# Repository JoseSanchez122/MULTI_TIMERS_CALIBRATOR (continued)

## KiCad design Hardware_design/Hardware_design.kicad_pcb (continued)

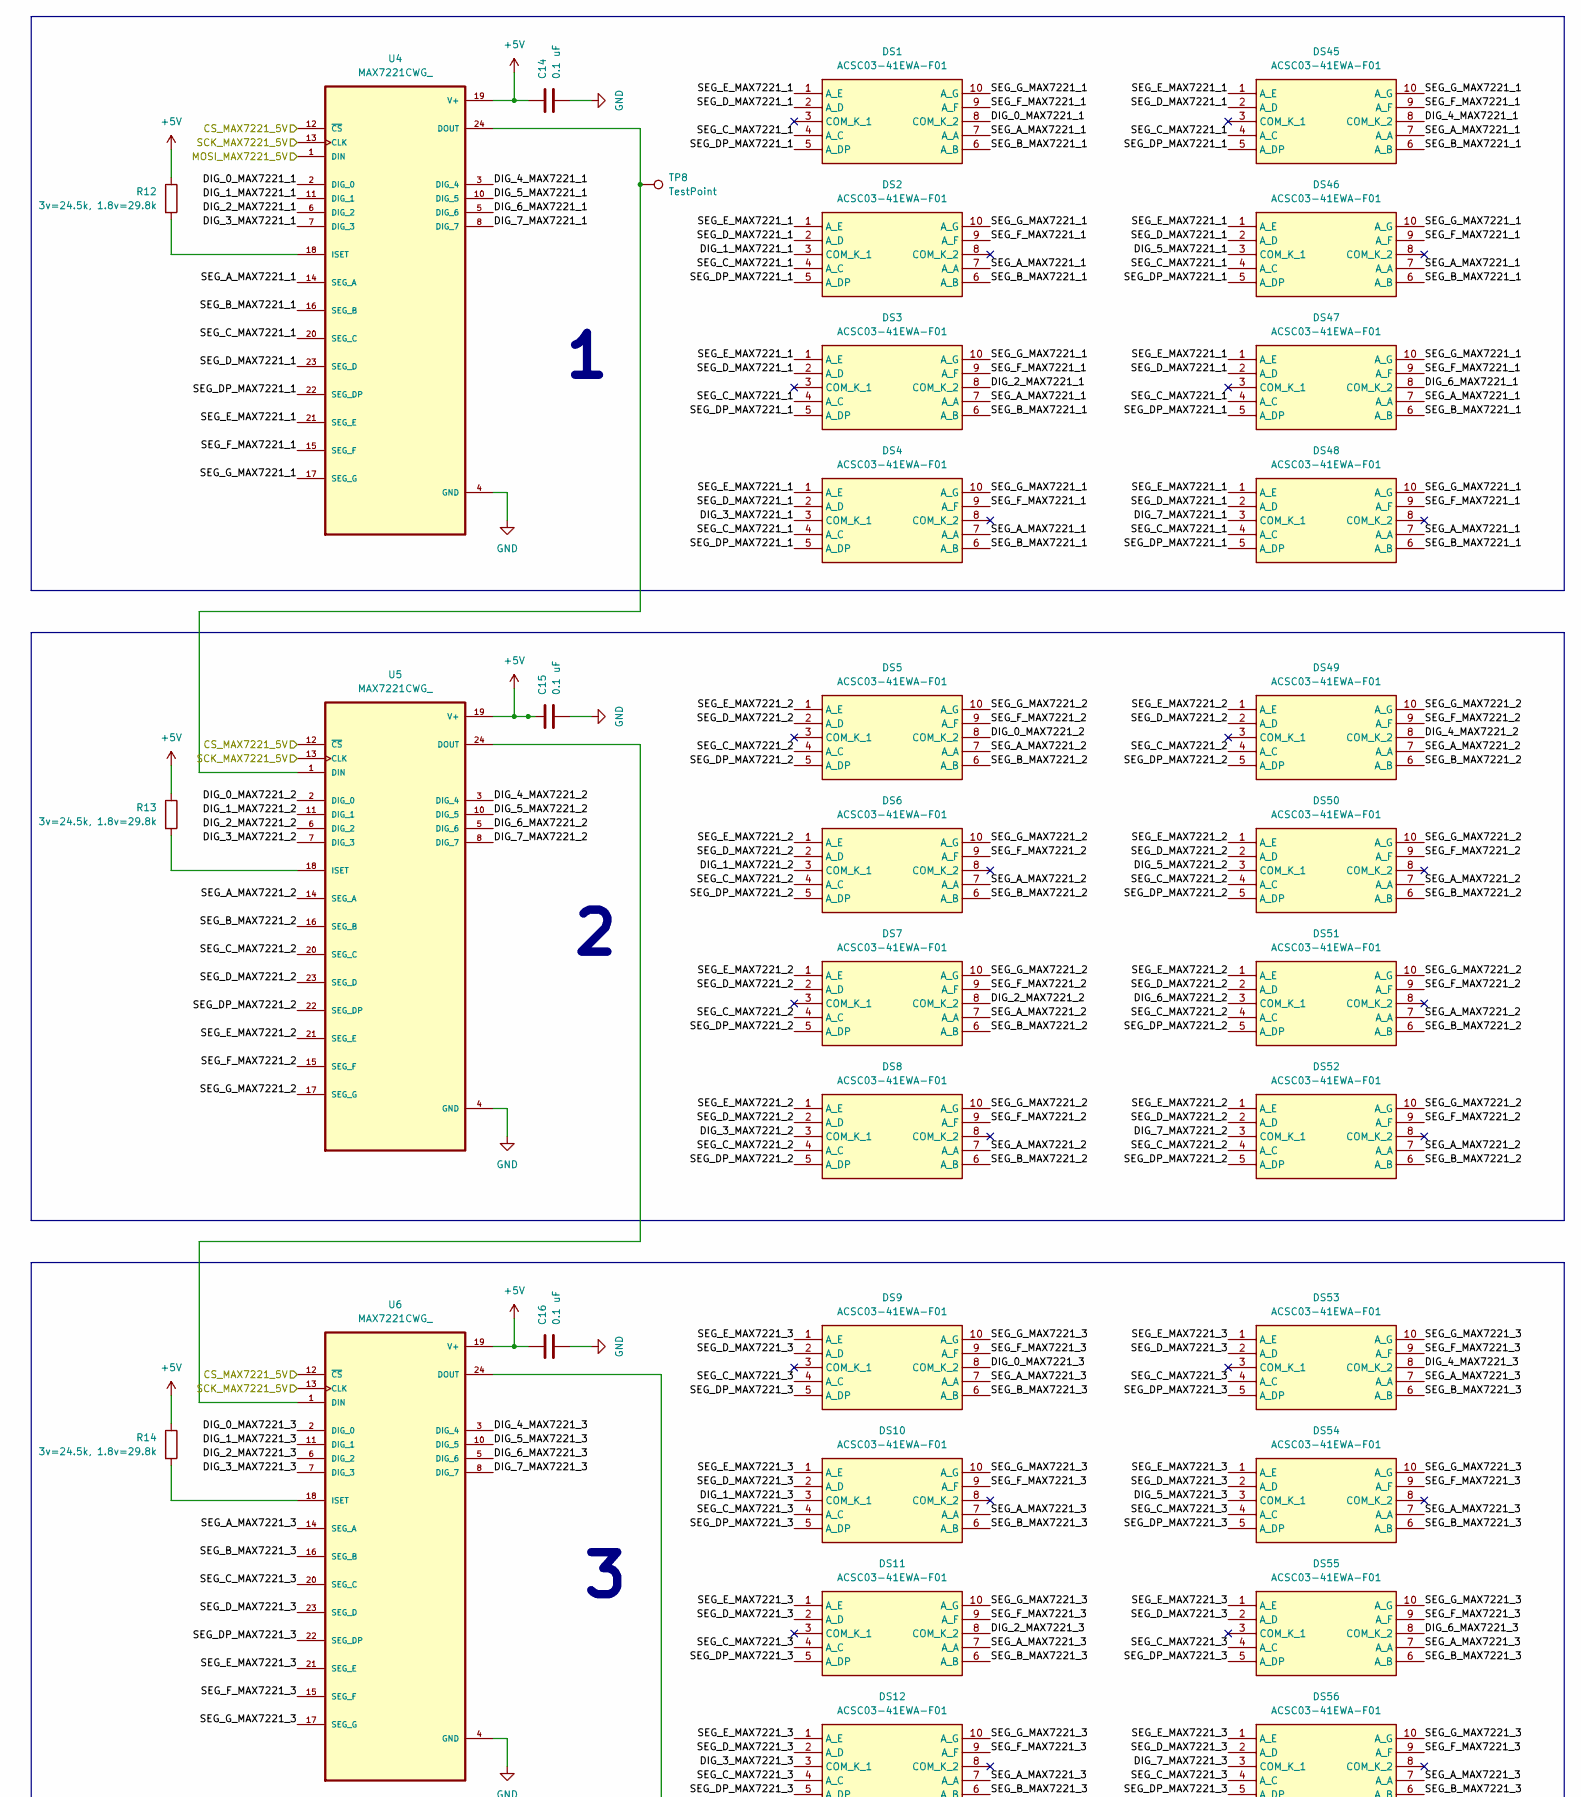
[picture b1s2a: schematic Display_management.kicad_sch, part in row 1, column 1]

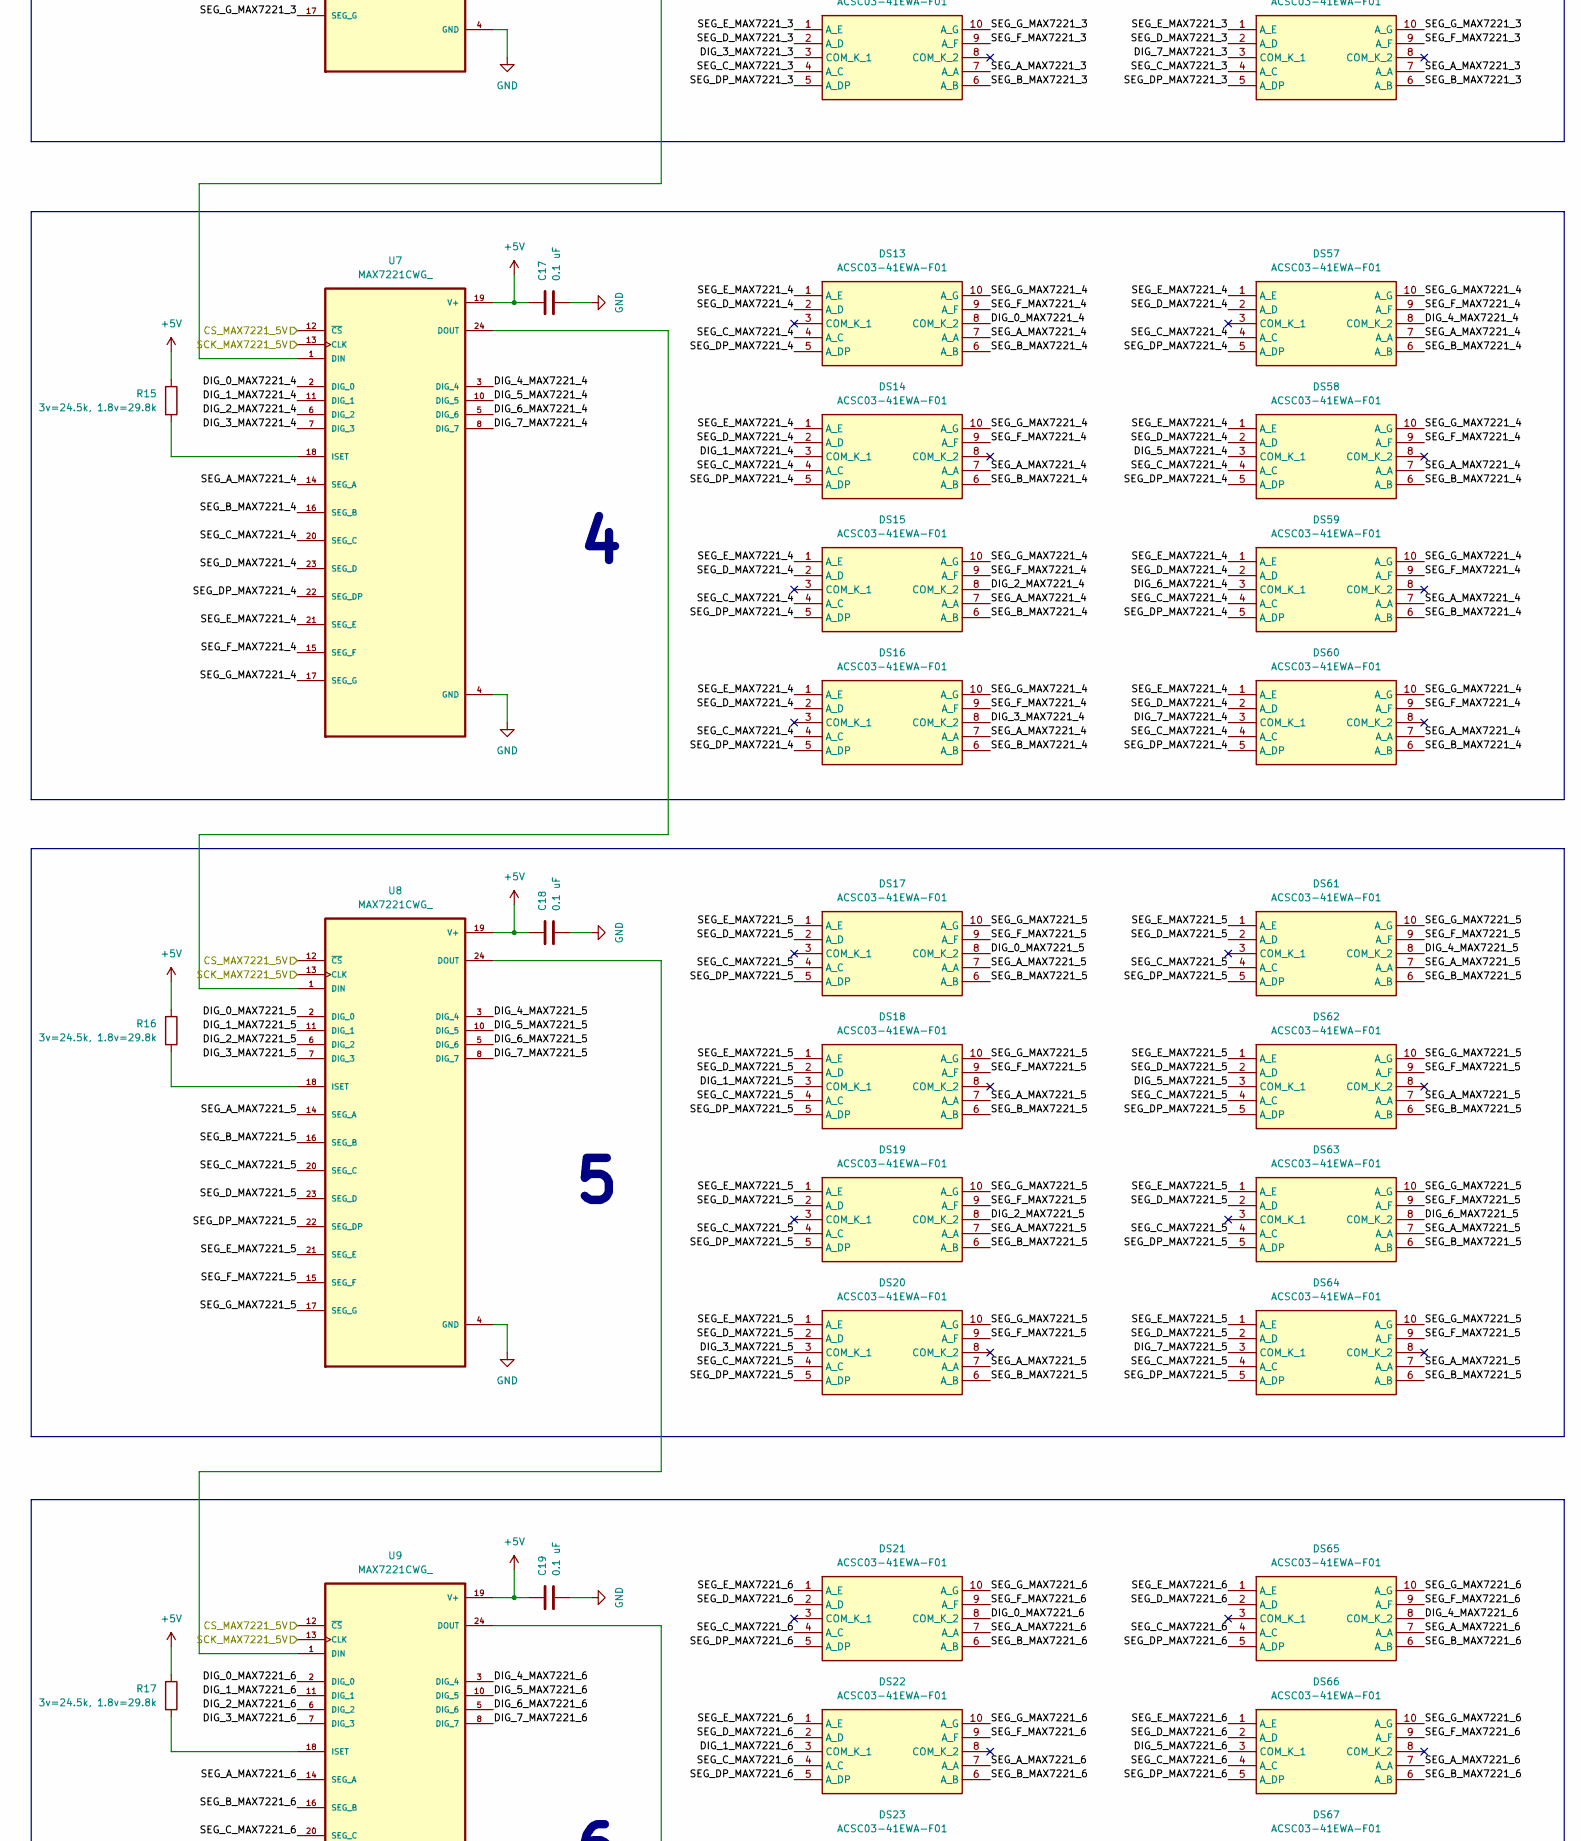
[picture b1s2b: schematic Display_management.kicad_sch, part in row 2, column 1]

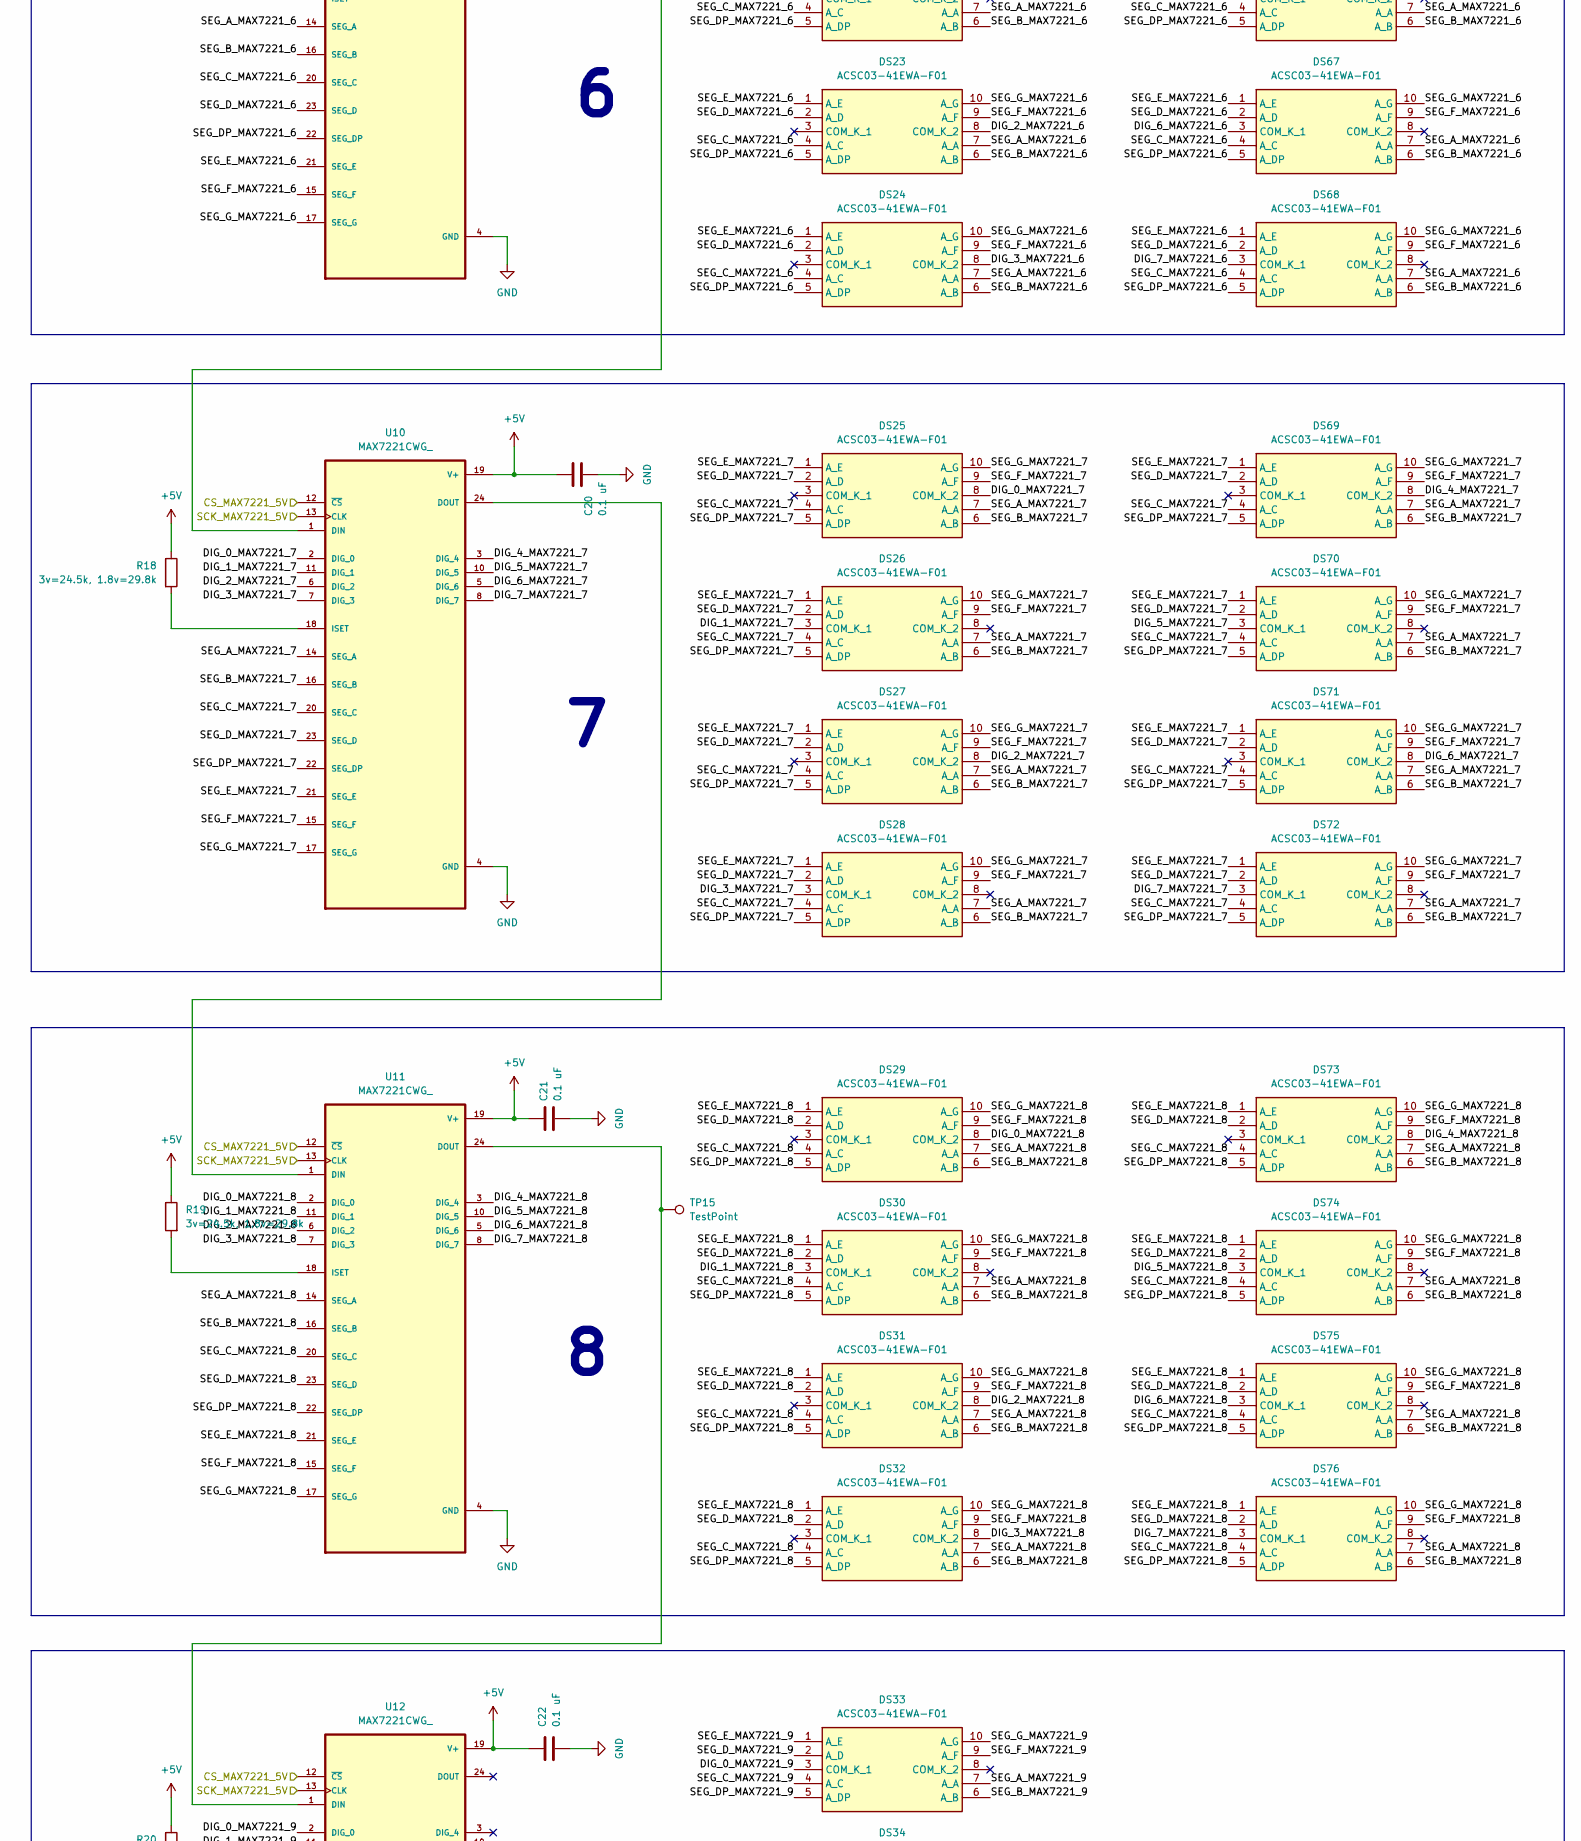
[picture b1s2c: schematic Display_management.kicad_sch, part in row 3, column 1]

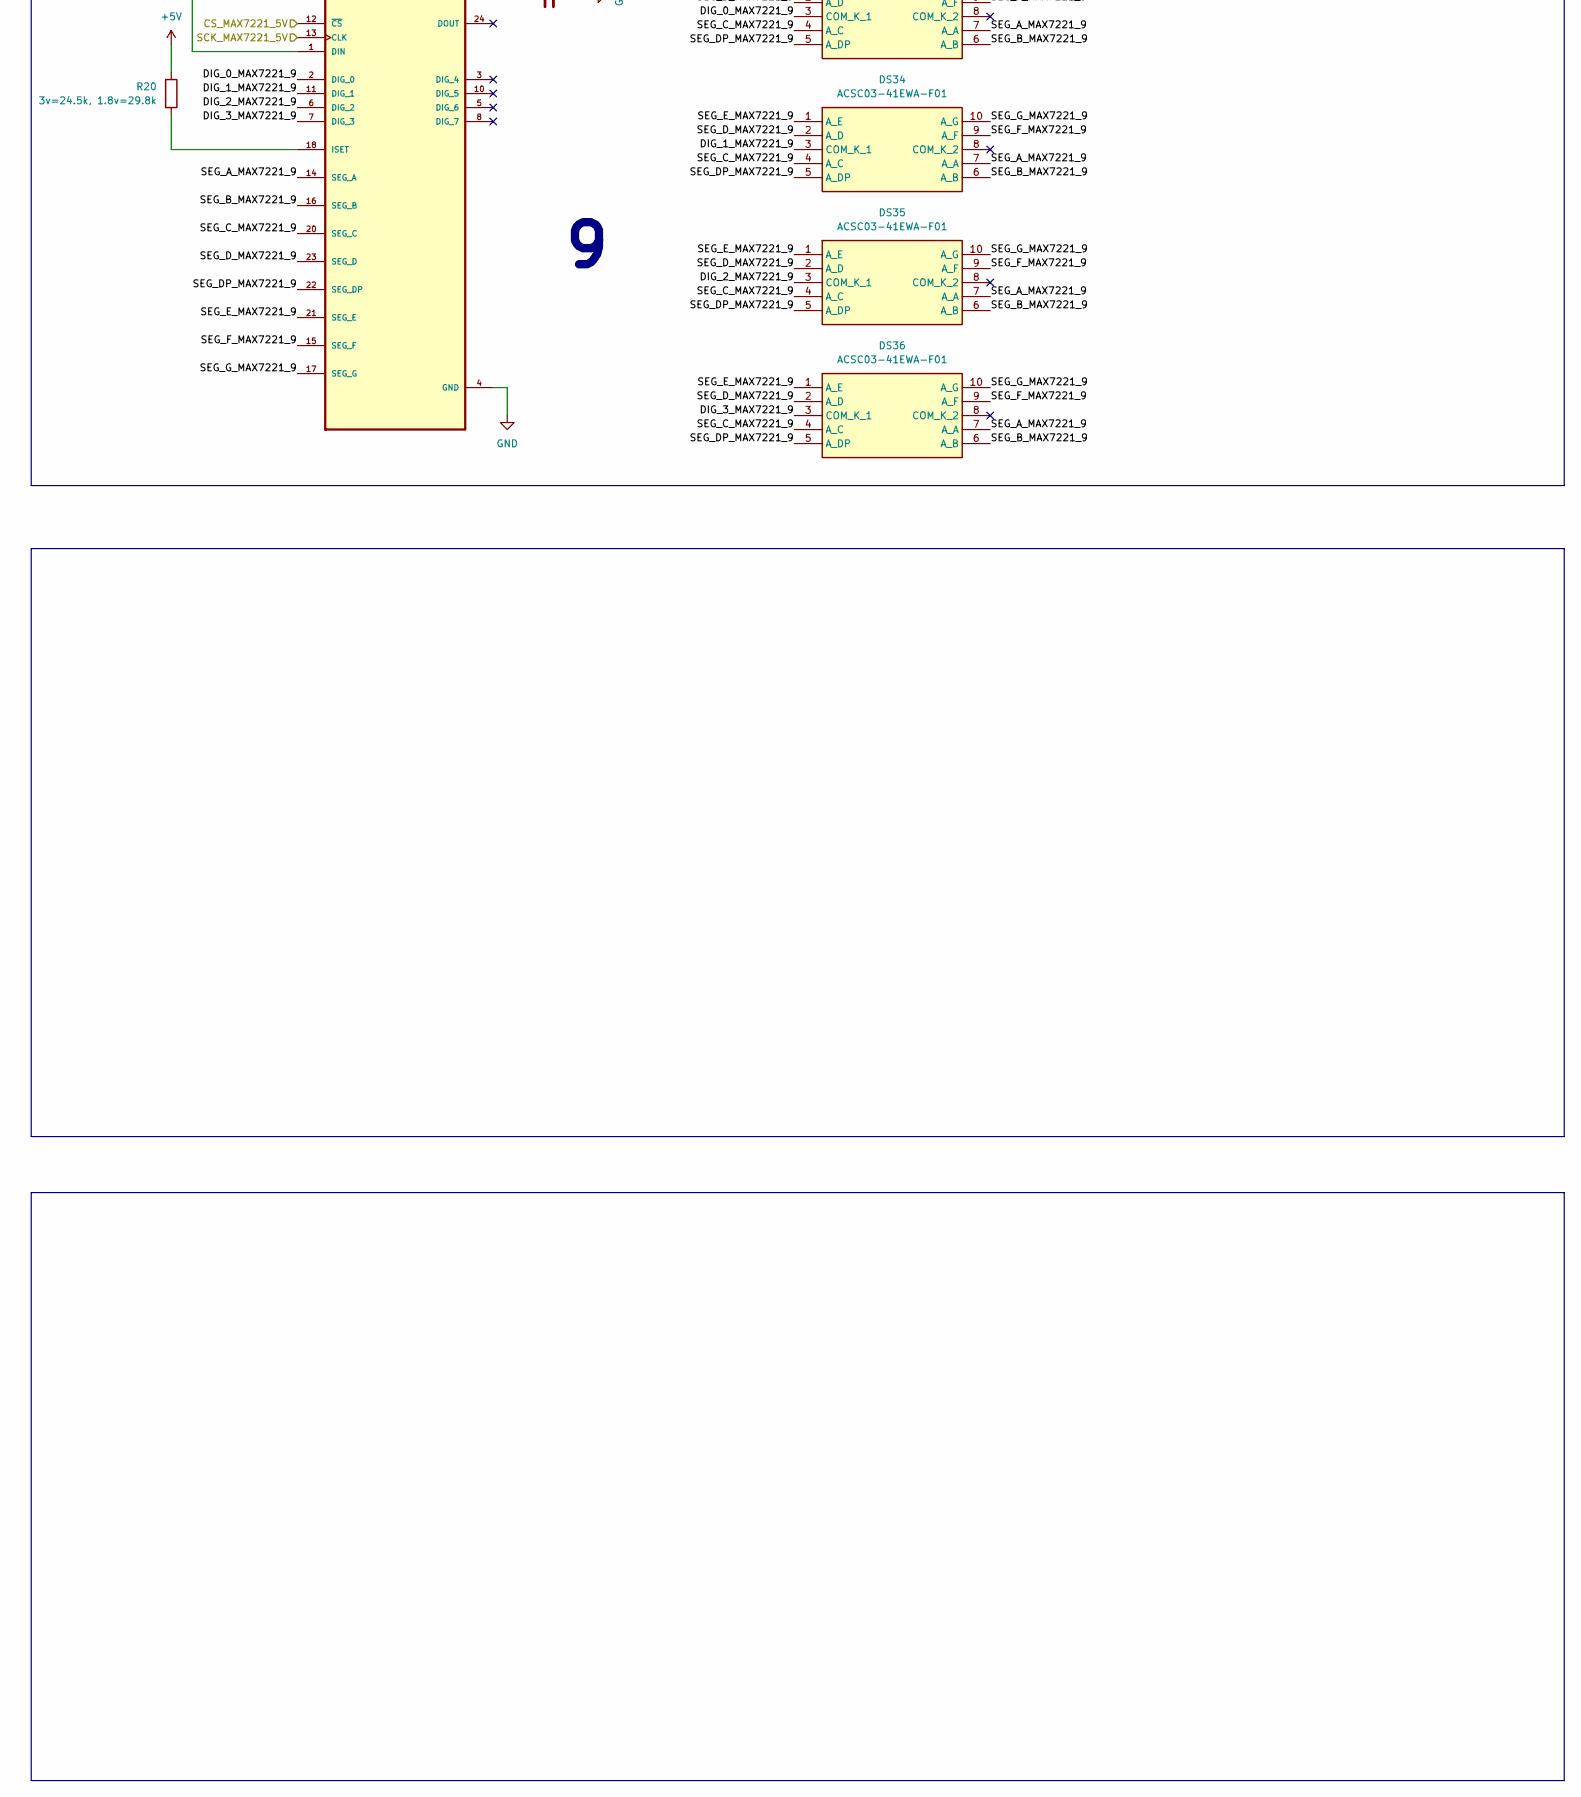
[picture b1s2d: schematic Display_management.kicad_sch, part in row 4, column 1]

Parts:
C14, C15, C16, C17, C18, C19, C20, C21, C22: 0.1 uF; 0805_SMD_CERAMIC_CAP_T491B106K016AT
DS1, DS2, DS3, DS4, DS5, DS6, DS7, DS8, DS9, DS10, DS11, DS12, DS13, DS14, DS15, DS16, DS17, DS18, DS19, DS20, DS21, DS22, DS23, DS24, DS25, DS26, DS27, DS28, DS29, DS30, DS31, DS32, DS33, DS34, DS35, DS36, DS45, DS46, DS47, DS48, DS49, DS50, DS51, DS52, DS53, DS54, DS55, DS56, DS57, DS58, DS59, DS60, DS61, DS62, DS63, DS64, DS65, DS66, DS67, DS68, DS69, DS70, DS71, DS72, DS73, DS74, DS75, DS76: ACSC03-41EWA-F01; SMD_DISPLAY_ACSC03-41EWA-F01; Mouser Part Number 604-ACSC03-41EWA-F01
R12, R13, R14, R15, R16, R17, R18, R19, R20: 3v=24.5k, 1.8v=29.8k; 0805_RES_RESC2012X60N
TP8, TP15: TestPoint; TestPoint_Pad_1.0x1.0mm
U4, U5, U6, U7, U8, U9, U10, U11, U12: MAX7221CWG_; Disp_Controler_MAX7221CWG_

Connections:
+5V: C14.1, C15.1, C16.1, C17.1, C18.1, C19.1, C20.1, C21.1, C22.1, R12.1, R13.1, R14.1, R15.1, R16.1, R17.1, R18.1, R19.1, R20.1, U4.19 (V+), U5.19 (V+), U6.19 (V+), U7.19 (V+), U8.19 (V+), U9.19 (V+), U10.19 (V+), U11.19 (V+), U12.19 (V+); also elsewhere on the board
/CS_MAX7221_5V: U4.12 (~CS), U5.12 (~CS), U6.12 (~CS), U7.12 (~CS), U8.12 (~CS), U9.12 (~CS), U10.12 (~CS), U11.12 (~CS), U12.12 (~CS); also elsewhere on the board
/Display_management/DIG_0_MAX7221_1: DS1.8 (COM_K_2), U4.2 (DIG_0)
/Display_management/DIG_0_MAX7221_2: DS5.8 (COM_K_2), U5.2 (DIG_0)
/Display_management/DIG_0_MAX7221_3: DS9.8 (COM_K_2), U6.2 (DIG_0)
/Display_management/DIG_0_MAX7221_4: DS13.8 (COM_K_2), U7.2 (DIG_0)
/Display_management/DIG_0_MAX7221_5: DS17.8 (COM_K_2), U8.2 (DIG_0)
/Display_management/DIG_0_MAX7221_6: DS21.8 (COM_K_2), U9.2 (DIG_0)
/Display_management/DIG_0_MAX7221_7: DS25.8 (COM_K_2), U10.2 (DIG_0)
/Display_management/DIG_0_MAX7221_8: DS29.8 (COM_K_2), U11.2 (DIG_0)
/Display_management/DIG_0_MAX7221_9: DS33.3 (COM_K_1), U12.2 (DIG_0)
/Display_management/DIG_1_MAX7221_1: DS2.3 (COM_K_1), U4.11 (DIG_1)
/Display_management/DIG_1_MAX7221_2: DS6.3 (COM_K_1), U5.11 (DIG_1)
/Display_management/DIG_1_MAX7221_3: DS10.3 (COM_K_1), U6.11 (DIG_1)
/Display_management/DIG_1_MAX7221_4: DS14.3 (COM_K_1), U7.11 (DIG_1)
/Display_management/DIG_1_MAX7221_5: DS18.3 (COM_K_1), U8.11 (DIG_1)
/Display_management/DIG_1_MAX7221_6: DS22.3 (COM_K_1), U9.11 (DIG_1)
/Display_management/DIG_1_MAX7221_7: DS26.3 (COM_K_1), U10.11 (DIG_1)
/Display_management/DIG_1_MAX7221_8: DS30.3 (COM_K_1), U11.11 (DIG_1)
/Display_management/DIG_1_MAX7221_9: DS34.3 (COM_K_1), U12.11 (DIG_1)
/Display_management/DIG_2_MAX7221_1: DS3.8 (COM_K_2), U4.6 (DIG_2)
/Display_management/DIG_2_MAX7221_2: DS7.8 (COM_K_2), U5.6 (DIG_2)
/Display_management/DIG_2_MAX7221_3: DS11.8 (COM_K_2), U6.6 (DIG_2)
/Display_management/DIG_2_MAX7221_4: DS15.8 (COM_K_2), U7.6 (DIG_2)
/Display_management/DIG_2_MAX7221_5: DS19.8 (COM_K_2), U8.6 (DIG_2)
/Display_management/DIG_2_MAX7221_6: DS23.8 (COM_K_2), U9.6 (DIG_2)
/Display_management/DIG_2_MAX7221_7: DS27.8 (COM_K_2), U10.6 (DIG_2)
/Display_management/DIG_2_MAX7221_8: DS31.8 (COM_K_2), U11.6 (DIG_2)
/Display_management/DIG_2_MAX7221_9: DS35.3 (COM_K_1), U12.6 (DIG_2)
/Display_management/DIG_3_MAX7221_1: DS4.3 (COM_K_1), U4.7 (DIG_3)
/Display_management/DIG_3_MAX7221_2: DS8.3 (COM_K_1), U5.7 (DIG_3)
/Display_management/DIG_3_MAX7221_3: DS12.3 (COM_K_1), U6.7 (DIG_3)
/Display_management/DIG_3_MAX7221_4: DS16.8 (COM_K_2), U7.7 (DIG_3)
/Display_management/DIG_3_MAX7221_5: DS20.3 (COM_K_1), U8.7 (DIG_3)
/Display_management/DIG_3_MAX7221_6: DS24.8 (COM_K_2), U9.7 (DIG_3)
/Display_management/DIG_3_MAX7221_7: DS28.3 (COM_K_1), U10.7 (DIG_3)
/Display_management/DIG_3_MAX7221_8: DS32.8 (COM_K_2), U11.7 (DIG_3)
/Display_management/DIG_3_MAX7221_9: DS36.3 (COM_K_1), U12.7 (DIG_3)
/Display_management/DIG_4_MAX7221_1: DS45.8 (COM_K_2), U4.3 (DIG_4)
/Display_management/DIG_4_MAX7221_2: DS49.8 (COM_K_2), U5.3 (DIG_4)
/Display_management/DIG_4_MAX7221_3: DS53.8 (COM_K_2), U6.3 (DIG_4)
/Display_management/DIG_4_MAX7221_4: DS57.8 (COM_K_2), U7.3 (DIG_4)
/Display_management/DIG_4_MAX7221_5: DS61.8 (COM_K_2), U8.3 (DIG_4)
/Display_management/DIG_4_MAX7221_6: DS65.8 (COM_K_2), U9.3 (DIG_4)
/Display_management/DIG_4_MAX7221_7: DS69.8 (COM_K_2), U10.3 (DIG_4)
/Display_management/DIG_4_MAX7221_8: DS73.8 (COM_K_2), U11.3 (DIG_4)
/Display_management/DIG_5_MAX7221_1: DS46.3 (COM_K_1), U4.10 (DIG_5)
/Display_management/DIG_5_MAX7221_2: DS50.3 (COM_K_1), U5.10 (DIG_5)
/Display_management/DIG_5_MAX7221_3: DS54.3 (COM_K_1), U6.10 (DIG_5)
/Display_management/DIG_5_MAX7221_4: DS58.3 (COM_K_1), U7.10 (DIG_5)
/Display_management/DIG_5_MAX7221_5: DS62.3 (COM_K_1), U8.10 (DIG_5)
/Display_management/DIG_5_MAX7221_6: DS66.3 (COM_K_1), U9.10 (DIG_5)
/Display_management/DIG_5_MAX7221_7: DS70.3 (COM_K_1), U10.10 (DIG_5)
/Display_management/DIG_5_MAX7221_8: DS74.3 (COM_K_1), U11.10 (DIG_5)
/Display_management/DIG_6_MAX7221_1: DS47.8 (COM_K_2), U4.5 (DIG_6)
/Display_management/DIG_6_MAX7221_2: DS51.3 (COM_K_1), U5.5 (DIG_6)
/Display_management/DIG_6_MAX7221_3: DS55.8 (COM_K_2), U6.5 (DIG_6)
/Display_management/DIG_6_MAX7221_4: DS59.3 (COM_K_1), U7.5 (DIG_6)
/Display_management/DIG_6_MAX7221_5: DS63.8 (COM_K_2), U8.5 (DIG_6)
/Display_management/DIG_6_MAX7221_6: DS67.3 (COM_K_1), U9.5 (DIG_6)
/Display_management/DIG_6_MAX7221_7: DS71.8 (COM_K_2), U10.5 (DIG_6)
/Display_management/DIG_6_MAX7221_8: DS75.3 (COM_K_1), U11.5 (DIG_6)
/Display_management/DIG_7_MAX7221_1: DS48.3 (COM_K_1), U4.8 (DIG_7)
/Display_management/DIG_7_MAX7221_2: DS52.3 (COM_K_1), U5.8 (DIG_7)
/Display_management/DIG_7_MAX7221_3: DS56.3 (COM_K_1), U6.8 (DIG_7)
/Display_management/DIG_7_MAX7221_4: DS60.3 (COM_K_1), U7.8 (DIG_7)
/Display_management/DIG_7_MAX7221_5: DS64.3 (COM_K_1), U8.8 (DIG_7)
/Display_management/DIG_7_MAX7221_6: DS68.3 (COM_K_1), U9.8 (DIG_7)
/Display_management/DIG_7_MAX7221_7: DS72.3 (COM_K_1), U10.8 (DIG_7)
/Display_management/DIG_7_MAX7221_8: DS76.3 (COM_K_1), U11.8 (DIG_7)
/Display_management/SEG_A_MAX7221_1: DS1.7 (A_A), DS2.7 (A_A), DS3.7 (A_A), DS4.7 (A_A), DS45.7 (A_A), DS46.7 (A_A), DS47.7 (A_A), DS48.7 (A_A), U4.14 (SEG_A)
/Display_management/SEG_A_MAX7221_2: DS5.7 (A_A), DS6.7 (A_A), DS7.7 (A_A), DS8.7 (A_A), DS49.7 (A_A), DS50.7 (A_A), DS51.7 (A_A), DS52.7 (A_A), U5.14 (SEG_A)
/Display_management/SEG_A_MAX7221_3: DS9.7 (A_A), DS10.7 (A_A), DS11.7 (A_A), DS12.7 (A_A), DS53.7 (A_A), DS54.7 (A_A), DS55.7 (A_A), DS56.7 (A_A), U6.14 (SEG_A)
/Display_management/SEG_A_MAX7221_4: DS13.7 (A_A), DS14.7 (A_A), DS15.7 (A_A), DS16.7 (A_A), DS57.7 (A_A), DS58.7 (A_A), DS59.7 (A_A), DS60.7 (A_A), U7.14 (SEG_A)
/Display_management/SEG_A_MAX7221_5: DS17.7 (A_A), DS18.7 (A_A), DS19.7 (A_A), DS20.7 (A_A), DS61.7 (A_A), DS62.7 (A_A), DS63.7 (A_A), DS64.7 (A_A), U8.14 (SEG_A)
/Display_management/SEG_A_MAX7221_6: DS21.7 (A_A), DS22.7 (A_A), DS23.7 (A_A), DS24.7 (A_A), DS65.7 (A_A), DS66.7 (A_A), DS67.7 (A_A), DS68.7 (A_A), U9.14 (SEG_A)
/Display_management/SEG_A_MAX7221_7: DS25.7 (A_A), DS26.7 (A_A), DS27.7 (A_A), DS28.7 (A_A), DS69.7 (A_A), DS70.7 (A_A), DS71.7 (A_A), DS72.7 (A_A), U10.14 (SEG_A)
/Display_management/SEG_A_MAX7221_8: DS29.7 (A_A), DS30.7 (A_A), DS31.7 (A_A), DS32.7 (A_A), DS73.7 (A_A), DS74.7 (A_A), DS75.7 (A_A), DS76.7 (A_A), U11.14 (SEG_A)
/Display_management/SEG_A_MAX7221_9: DS33.7 (A_A), DS34.7 (A_A), DS35.7 (A_A), DS36.7 (A_A), U12.14 (SEG_A)
/Display_management/SEG_B_MAX7221_1: DS1.6 (A_B), DS2.6 (A_B), DS3.6 (A_B), DS4.6 (A_B), DS45.6 (A_B), DS46.6 (A_B), DS47.6 (A_B), DS48.6 (A_B), U4.16 (SEG_B)
/Display_management/SEG_B_MAX7221_2: DS5.6 (A_B), DS6.6 (A_B), DS7.6 (A_B), DS8.6 (A_B), DS49.6 (A_B), DS50.6 (A_B), DS51.6 (A_B), DS52.6 (A_B), U5.16 (SEG_B)
/Display_management/SEG_B_MAX7221_3: DS9.6 (A_B), DS10.6 (A_B), DS11.6 (A_B), DS12.6 (A_B), DS53.6 (A_B), DS54.6 (A_B), DS55.6 (A_B), DS56.6 (A_B), U6.16 (SEG_B)
/Display_management/SEG_B_MAX7221_4: DS13.6 (A_B), DS14.6 (A_B), DS15.6 (A_B), DS16.6 (A_B), DS57.6 (A_B), DS58.6 (A_B), DS59.6 (A_B), DS60.6 (A_B), U7.16 (SEG_B)
/Display_management/SEG_B_MAX7221_5: DS17.6 (A_B), DS18.6 (A_B), DS19.6 (A_B), DS20.6 (A_B), DS61.6 (A_B), DS62.6 (A_B), DS63.6 (A_B), DS64.6 (A_B), U8.16 (SEG_B)
/Display_management/SEG_B_MAX7221_6: DS21.6 (A_B), DS22.6 (A_B), DS23.6 (A_B), DS24.6 (A_B), DS65.6 (A_B), DS66.6 (A_B), DS67.6 (A_B), DS68.6 (A_B), U9.16 (SEG_B)
/Display_management/SEG_B_MAX7221_7: DS25.6 (A_B), DS26.6 (A_B), DS27.6 (A_B), DS28.6 (A_B), DS69.6 (A_B), DS70.6 (A_B), DS71.6 (A_B), DS72.6 (A_B), U10.16 (SEG_B)
/Display_management/SEG_B_MAX7221_8: DS29.6 (A_B), DS30.6 (A_B), DS31.6 (A_B), DS32.6 (A_B), DS73.6 (A_B), DS74.6 (A_B), DS75.6 (A_B), DS76.6 (A_B), U11.16 (SEG_B)
/Display_management/SEG_B_MAX7221_9: DS33.6 (A_B), DS34.6 (A_B), DS35.6 (A_B), DS36.6 (A_B), U12.16 (SEG_B)
/Display_management/SEG_C_MAX7221_1: DS1.4 (A_C), DS2.4 (A_C), DS3.4 (A_C), DS4.4 (A_C), DS45.4 (A_C), DS46.4 (A_C), DS47.4 (A_C), DS48.4 (A_C), U4.20 (SEG_C)
/Display_management/SEG_C_MAX7221_2: DS5.4 (A_C), DS6.4 (A_C), DS7.4 (A_C), DS8.4 (A_C), DS49.4 (A_C), DS50.4 (A_C), DS51.4 (A_C), DS52.4 (A_C), U5.20 (SEG_C)
/Display_management/SEG_C_MAX7221_3: DS9.4 (A_C), DS10.4 (A_C), DS11.4 (A_C), DS12.4 (A_C), DS53.4 (A_C), DS54.4 (A_C), DS55.4 (A_C), DS56.4 (A_C), U6.20 (SEG_C)
/Display_management/SEG_C_MAX7221_4: DS13.4 (A_C), DS14.4 (A_C), DS15.4 (A_C), DS16.4 (A_C), DS57.4 (A_C), DS58.4 (A_C), DS59.4 (A_C), DS60.4 (A_C), U7.20 (SEG_C)
/Display_management/SEG_C_MAX7221_5: DS17.4 (A_C), DS18.4 (A_C), DS19.4 (A_C), DS20.4 (A_C), DS61.4 (A_C), DS62.4 (A_C), DS63.4 (A_C), DS64.4 (A_C), U8.20 (SEG_C)
/Display_management/SEG_C_MAX7221_6: DS21.4 (A_C), DS22.4 (A_C), DS23.4 (A_C), DS24.4 (A_C), DS65.4 (A_C), DS66.4 (A_C), DS67.4 (A_C), DS68.4 (A_C), U9.20 (SEG_C)
/Display_management/SEG_C_MAX7221_7: DS25.4 (A_C), DS26.4 (A_C), DS27.4 (A_C), DS28.4 (A_C), DS69.4 (A_C), DS70.4 (A_C), DS71.4 (A_C), DS72.4 (A_C), U10.20 (SEG_C)
/Display_management/SEG_C_MAX7221_8: DS29.4 (A_C), DS30.4 (A_C), DS31.4 (A_C), DS32.4 (A_C), DS73.4 (A_C), DS74.4 (A_C), DS75.4 (A_C), DS76.4 (A_C), U11.20 (SEG_C)
/Display_management/SEG_C_MAX7221_9: DS33.4 (A_C), DS34.4 (A_C), DS35.4 (A_C), DS36.4 (A_C), U12.20 (SEG_C)
/Display_management/SEG_DP_MAX7221_1: DS1.5 (A_DP), DS2.5 (A_DP), DS3.5 (A_DP), DS4.5 (A_DP), DS45.5 (A_DP), DS46.5 (A_DP), DS47.5 (A_DP), DS48.5 (A_DP), U4.22 (SEG_DP)
/Display_management/SEG_DP_MAX7221_2: DS5.5 (A_DP), DS6.5 (A_DP), DS7.5 (A_DP), DS8.5 (A_DP), DS49.5 (A_DP), DS50.5 (A_DP), DS51.5 (A_DP), DS52.5 (A_DP), U5.22 (SEG_DP)
/Display_management/SEG_DP_MAX7221_3: DS9.5 (A_DP), DS10.5 (A_DP), DS11.5 (A_DP), DS12.5 (A_DP), DS53.5 (A_DP), DS54.5 (A_DP), DS55.5 (A_DP), DS56.5 (A_DP), U6.22 (SEG_DP)
/Display_management/SEG_DP_MAX7221_4: DS13.5 (A_DP), DS14.5 (A_DP), DS15.5 (A_DP), DS16.5 (A_DP), DS57.5 (A_DP), DS58.5 (A_DP), DS59.5 (A_DP), DS60.5 (A_DP), U7.22 (SEG_DP)
/Display_management/SEG_DP_MAX7221_5: DS17.5 (A_DP), DS18.5 (A_DP), DS19.5 (A_DP), DS20.5 (A_DP), DS61.5 (A_DP), DS62.5 (A_DP), DS63.5 (A_DP), DS64.5 (A_DP), U8.22 (SEG_DP)
/Display_management/SEG_DP_MAX7221_6: DS21.5 (A_DP), DS22.5 (A_DP), DS23.5 (A_DP), DS24.5 (A_DP), DS65.5 (A_DP), DS66.5 (A_DP), DS67.5 (A_DP), DS68.5 (A_DP), U9.22 (SEG_DP)
/Display_management/SEG_DP_MAX7221_7: DS25.5 (A_DP), DS26.5 (A_DP), DS27.5 (A_DP), DS28.5 (A_DP), DS69.5 (A_DP), DS70.5 (A_DP), DS71.5 (A_DP), DS72.5 (A_DP), U10.22 (SEG_DP)
/Display_management/SEG_DP_MAX7221_8: DS29.5 (A_DP), DS30.5 (A_DP), DS31.5 (A_DP), DS32.5 (A_DP), DS73.5 (A_DP), DS74.5 (A_DP), DS75.5 (A_DP), DS76.5 (A_DP), U11.22 (SEG_DP)
/Display_management/SEG_DP_MAX7221_9: DS33.5 (A_DP), DS34.5 (A_DP), DS35.5 (A_DP), DS36.5 (A_DP), U12.22 (SEG_DP)
/Display_management/SEG_D_MAX7221_1: DS1.2 (A_D), DS2.2 (A_D), DS3.2 (A_D), DS4.2 (A_D), DS45.2 (A_D), DS46.2 (A_D), DS47.2 (A_D), DS48.2 (A_D), U4.23 (SEG_D)
/Display_management/SEG_D_MAX7221_2: DS5.2 (A_D), DS6.2 (A_D), DS7.2 (A_D), DS8.2 (A_D), DS49.2 (A_D), DS50.2 (A_D), DS51.2 (A_D), DS52.2 (A_D), U5.23 (SEG_D)
/Display_management/SEG_D_MAX7221_3: DS9.2 (A_D), DS10.2 (A_D), DS11.2 (A_D), DS12.2 (A_D), DS53.2 (A_D), DS54.2 (A_D), DS55.2 (A_D), DS56.2 (A_D), U6.23 (SEG_D)
/Display_management/SEG_D_MAX7221_4: DS13.2 (A_D), DS14.2 (A_D), DS15.2 (A_D), DS16.2 (A_D), DS57.2 (A_D), DS58.2 (A_D), DS59.2 (A_D), DS60.2 (A_D), U7.23 (SEG_D)
/Display_management/SEG_D_MAX7221_5: DS17.2 (A_D), DS18.2 (A_D), DS19.2 (A_D), DS20.2 (A_D), DS61.2 (A_D), DS62.2 (A_D), DS63.2 (A_D), DS64.2 (A_D), U8.23 (SEG_D)
/Display_management/SEG_D_MAX7221_6: DS21.2 (A_D), DS22.2 (A_D), DS23.2 (A_D), DS24.2 (A_D), DS65.2 (A_D), DS66.2 (A_D), DS67.2 (A_D), DS68.2 (A_D), U9.23 (SEG_D)
/Display_management/SEG_D_MAX7221_7: DS25.2 (A_D), DS26.2 (A_D), DS27.2 (A_D), DS28.2 (A_D), DS69.2 (A_D), DS70.2 (A_D), DS71.2 (A_D), DS72.2 (A_D), U10.23 (SEG_D)
/Display_management/SEG_D_MAX7221_8: DS29.2 (A_D), DS30.2 (A_D), DS31.2 (A_D), DS32.2 (A_D), DS73.2 (A_D), DS74.2 (A_D), DS75.2 (A_D), DS76.2 (A_D), U11.23 (SEG_D)
/Display_management/SEG_D_MAX7221_9: DS33.2 (A_D), DS34.2 (A_D), DS35.2 (A_D), DS36.2 (A_D), U12.23 (SEG_D)
/Display_management/SEG_E_MAX7221_1: DS1.1 (A_E), DS2.1 (A_E), DS3.1 (A_E), DS4.1 (A_E), DS45.1 (A_E), DS46.1 (A_E), DS47.1 (A_E), DS48.1 (A_E), U4.21 (SEG_E)
/Display_management/SEG_E_MAX7221_2: DS5.1 (A_E), DS6.1 (A_E), DS7.1 (A_E), DS8.1 (A_E), DS49.1 (A_E), DS50.1 (A_E), DS51.1 (A_E), DS52.1 (A_E), U5.21 (SEG_E)
/Display_management/SEG_E_MAX7221_3: DS9.1 (A_E), DS10.1 (A_E), DS11.1 (A_E), DS12.1 (A_E), DS53.1 (A_E), DS54.1 (A_E), DS55.1 (A_E), DS56.1 (A_E), U6.21 (SEG_E)
/Display_management/SEG_E_MAX7221_4: DS13.1 (A_E), DS14.1 (A_E), DS15.1 (A_E), DS16.1 (A_E), DS57.1 (A_E), DS58.1 (A_E), DS59.1 (A_E), DS60.1 (A_E), U7.21 (SEG_E)
/Display_management/SEG_E_MAX7221_5: DS17.1 (A_E), DS18.1 (A_E), DS19.1 (A_E), DS20.1 (A_E), DS61.1 (A_E), DS62.1 (A_E), DS63.1 (A_E), DS64.1 (A_E), U8.21 (SEG_E)
/Display_management/SEG_E_MAX7221_6: DS21.1 (A_E), DS22.1 (A_E), DS23.1 (A_E), DS24.1 (A_E), DS65.1 (A_E), DS66.1 (A_E), DS67.1 (A_E), DS68.1 (A_E), U9.21 (SEG_E)
/Display_management/SEG_E_MAX7221_7: DS25.1 (A_E), DS26.1 (A_E), DS27.1 (A_E), DS28.1 (A_E), DS69.1 (A_E), DS70.1 (A_E), DS71.1 (A_E), DS72.1 (A_E), U10.21 (SEG_E)
/Display_management/SEG_E_MAX7221_8: DS29.1 (A_E), DS30.1 (A_E), DS31.1 (A_E), DS32.1 (A_E), DS73.1 (A_E), DS74.1 (A_E), DS75.1 (A_E), DS76.1 (A_E), U11.21 (SEG_E)
/Display_management/SEG_E_MAX7221_9: DS33.1 (A_E), DS34.1 (A_E), DS35.1 (A_E), DS36.1 (A_E), U12.21 (SEG_E)
/Display_management/SEG_F_MAX7221_1: DS1.9 (A_F), DS2.9 (A_F), DS3.9 (A_F), DS4.9 (A_F), DS45.9 (A_F), DS46.9 (A_F), DS47.9 (A_F), DS48.9 (A_F), U4.15 (SEG_F)
/Display_management/SEG_F_MAX7221_2: DS5.9 (A_F), DS6.9 (A_F), DS7.9 (A_F), DS8.9 (A_F), DS49.9 (A_F), DS50.9 (A_F), DS51.9 (A_F), DS52.9 (A_F), U5.15 (SEG_F)
/Display_management/SEG_F_MAX7221_3: DS9.9 (A_F), DS10.9 (A_F), DS11.9 (A_F), DS12.9 (A_F), DS53.9 (A_F), DS54.9 (A_F), DS55.9 (A_F), DS56.9 (A_F), U6.15 (SEG_F)
/Display_management/SEG_F_MAX7221_4: DS13.9 (A_F), DS14.9 (A_F), DS15.9 (A_F), DS16.9 (A_F), DS57.9 (A_F), DS58.9 (A_F), DS59.9 (A_F), DS60.9 (A_F), U7.15 (SEG_F)
/Display_management/SEG_F_MAX7221_5: DS17.9 (A_F), DS18.9 (A_F), DS19.9 (A_F), DS20.9 (A_F), DS61.9 (A_F), DS62.9 (A_F), DS63.9 (A_F), DS64.9 (A_F), U8.15 (SEG_F)
/Display_management/SEG_F_MAX7221_6: DS21.9 (A_F), DS22.9 (A_F), DS23.9 (A_F), DS24.9 (A_F), DS65.9 (A_F), DS66.9 (A_F), DS67.9 (A_F), DS68.9 (A_F), U9.15 (SEG_F)
/Display_management/SEG_F_MAX7221_7: DS25.9 (A_F), DS26.9 (A_F), DS27.9 (A_F), DS28.9 (A_F), DS69.9 (A_F), DS70.9 (A_F), DS71.9 (A_F), DS72.9 (A_F), U10.15 (SEG_F)
/Display_management/SEG_F_MAX7221_8: DS29.9 (A_F), DS30.9 (A_F), DS31.9 (A_F), DS32.9 (A_F), DS73.9 (A_F), DS74.9 (A_F), DS75.9 (A_F), DS76.9 (A_F), U11.15 (SEG_F)
/Display_management/SEG_F_MAX7221_9: DS33.9 (A_F), DS34.9 (A_F), DS35.9 (A_F), DS36.9 (A_F), U12.15 (SEG_F)
/Display_management/SEG_G_MAX7221_1: DS1.10 (A_G), DS2.10 (A_G), DS3.10 (A_G), DS4.10 (A_G), DS45.10 (A_G), DS46.10 (A_G), DS47.10 (A_G), DS48.10 (A_G), U4.17 (SEG_G)
/Display_management/SEG_G_MAX7221_2: DS5.10 (A_G), DS6.10 (A_G), DS7.10 (A_G), DS8.10 (A_G), DS49.10 (A_G), DS50.10 (A_G), DS51.10 (A_G), DS52.10 (A_G), U5.17 (SEG_G)
/Display_management/SEG_G_MAX7221_3: DS9.10 (A_G), DS10.10 (A_G), DS11.10 (A_G), DS12.10 (A_G), DS53.10 (A_G), DS54.10 (A_G), DS55.10 (A_G), DS56.10 (A_G), U6.17 (SEG_G)
/Display_management/SEG_G_MAX7221_4: DS13.10 (A_G), DS14.10 (A_G), DS15.10 (A_G), DS16.10 (A_G), DS57.10 (A_G), DS58.10 (A_G), DS59.10 (A_G), DS60.10 (A_G), U7.17 (SEG_G)
/Display_management/SEG_G_MAX7221_5: DS17.10 (A_G), DS18.10 (A_G), DS19.10 (A_G), DS20.10 (A_G), DS61.10 (A_G), DS62.10 (A_G), DS63.10 (A_G), DS64.10 (A_G), U8.17 (SEG_G)
/Display_management/SEG_G_MAX7221_6: DS21.10 (A_G), DS22.10 (A_G), DS23.10 (A_G), DS24.10 (A_G), DS65.10 (A_G), DS66.10 (A_G), DS67.10 (A_G), DS68.10 (A_G), U9.17 (SEG_G)
/Display_management/SEG_G_MAX7221_7: DS25.10 (A_G), DS26.10 (A_G), DS27.10 (A_G), DS28.10 (A_G), DS69.10 (A_G), DS70.10 (A_G), DS71.10 (A_G), DS72.10 (A_G), U10.17 (SEG_G)
/Display_management/SEG_G_MAX7221_8: DS29.10 (A_G), DS30.10 (A_G), DS31.10 (A_G), DS32.10 (A_G), DS73.10 (A_G), DS74.10 (A_G), DS75.10 (A_G), DS76.10 (A_G), U11.17 (SEG_G)
/Display_management/SEG_G_MAX7221_9: DS33.10 (A_G), DS34.10 (A_G), DS35.10 (A_G), DS36.10 (A_G), U12.17 (SEG_G)
/MOSI_MAX7221_5V: U4.1 (DIN); also elsewhere on the board
/SCK_MAX7221_5V: U4.13 (CLK), U5.13 (CLK), U6.13 (CLK), U7.13 (CLK), U8.13 (CLK), U9.13 (CLK), U10.13 (CLK), U11.13 (CLK), U12.13 (CLK); also elsewhere on the board
GND: C14.2, C15.2, C16.2, C17.2, C18.2, C19.2, C20.2, C21.2, C22.2, U4.4 (GND), U4.9 (GND), U5.4 (GND), U5.9 (GND), U6.4 (GND), U6.9 (GND), U7.4 (GND), U7.9 (GND), U8.4 (GND), U8.9 (GND), U9.4 (GND), U9.9 (GND), U10.4 (GND), U10.9 (GND), U11.4 (GND), U11.9 (GND), U12.4 (GND), U12.9 (GND); also elsewhere on the board
unnamed: TP8.1 (1_1), U4.24 (DOUT), U5.1 (DIN)
unnamed: R12.2, U4.18 (ISET)
unnamed: U5.24 (DOUT), U6.1 (DIN)
unnamed: R13.2, U5.18 (ISET)
unnamed: U6.24 (DOUT), U7.1 (DIN)
unnamed: R14.2, U6.18 (ISET)
unnamed: U7.24 (DOUT), U8.1 (DIN)
unnamed: R15.2, U7.18 (ISET)
unnamed: U8.24 (DOUT), U9.1 (DIN)
unnamed: R16.2, U8.18 (ISET)
unnamed: R17.2, U9.18 (ISET)
unnamed: U9.24 (DOUT), U10.1 (DIN)
unnamed: U10.24 (DOUT), U11.1 (DIN)
unnamed: R18.2, U10.18 (ISET)
unnamed: TP15.1 (1_1), U11.24 (DOUT), U12.1 (DIN)
unnamed: R19.2, U11.18 (ISET)
unnamed: R20.2, U12.18 (ISET)
